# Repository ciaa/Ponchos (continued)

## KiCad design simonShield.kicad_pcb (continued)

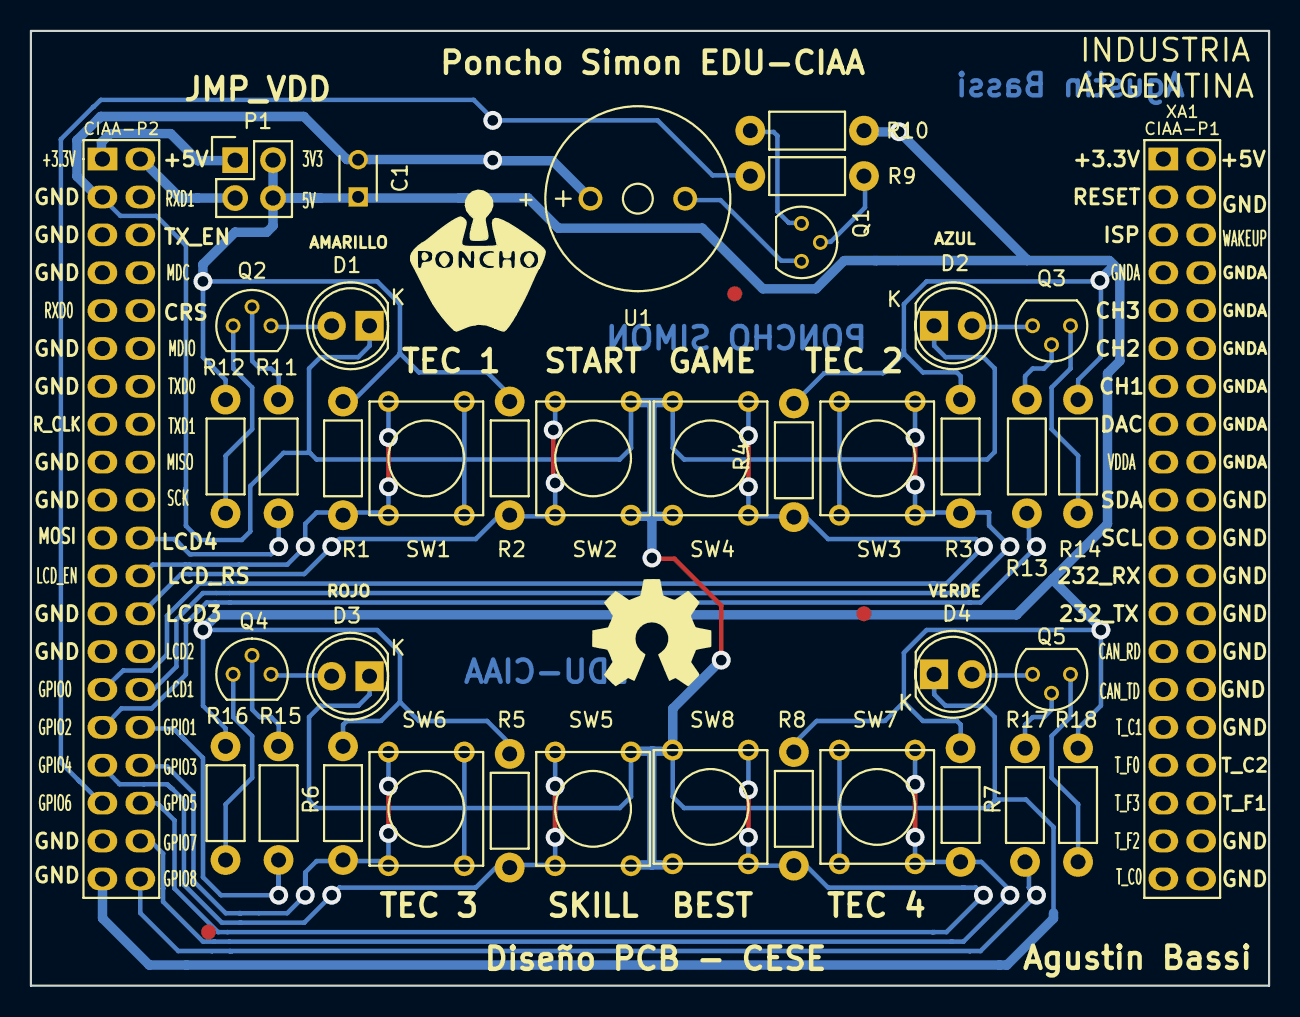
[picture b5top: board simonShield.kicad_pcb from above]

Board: 2 copper layers, 83.0 x 64.0 mm, 43 parts (0 on the bottom side), 32 nets.

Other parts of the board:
G101: Logo_OSHWA

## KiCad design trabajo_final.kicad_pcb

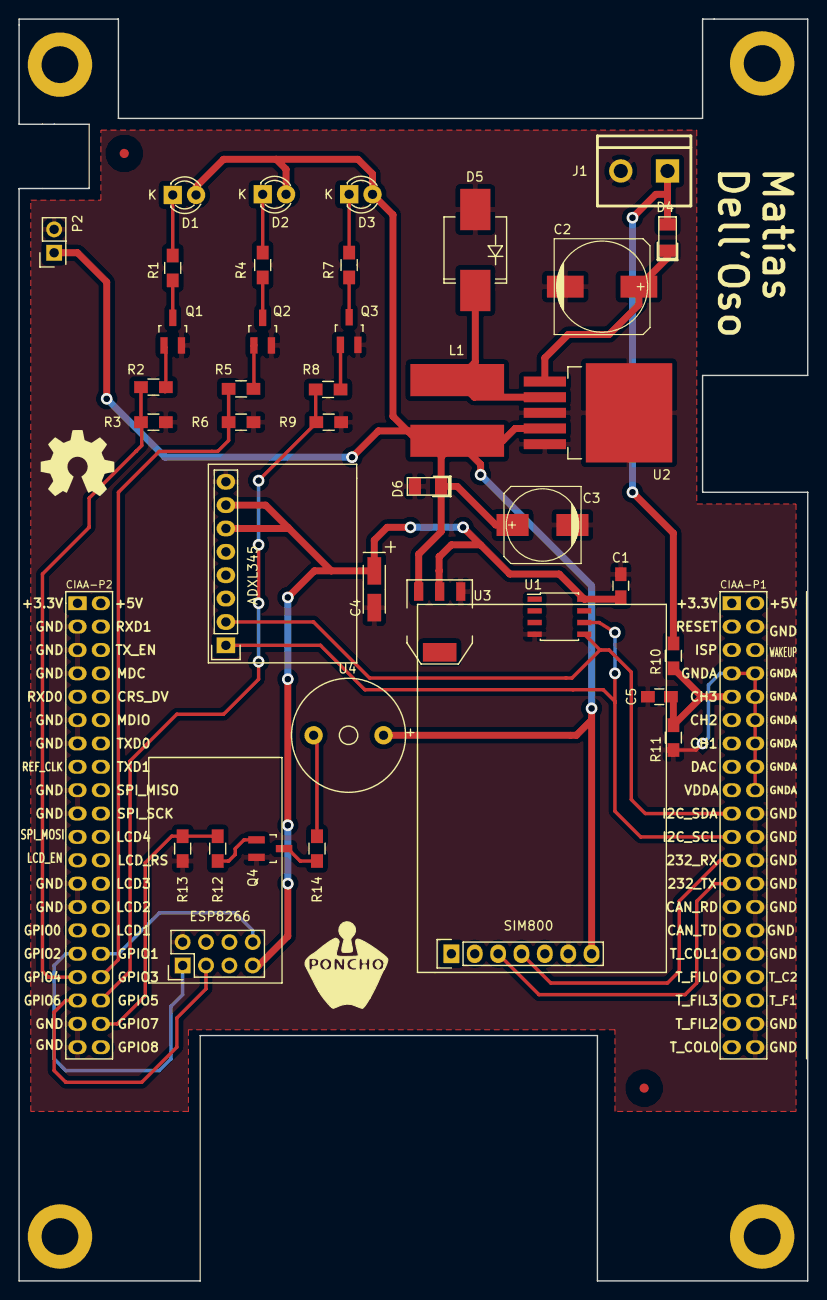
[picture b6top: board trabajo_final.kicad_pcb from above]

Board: 2 copper layers, 85.7 x 137.2 mm, 43 parts (0 on the bottom side), 30 nets.

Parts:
ADXL345: CONN_01X08; adxl345
C1, C5: 100nF; C_0805_HandSoldering
C2: 470uF; c2
C3: 330uF; c3
C4: 10uF; TantalC_SizeA_EIA-3216_HandSoldering
D1, D2, D3: LED; LED-3MM
D4: PMEG3020EH; SOD123F
D5: B540C-13-F; SMC_Handsoldering
D6: SMAZ5V6; SOD123F
ESP8266: CONN_02X04; esp8266
F1, F2: FIDUCIAL; Fiducial_1mm
G101: Logo_OSHWA
J1: TB_1X2; bornier2
L1: 47uH; SRN1060
P2: CONN_02X01; Pin_Header_Straight_2x01
Q1, Q2, Q3, Q4: 2N7002; SOT-23_Handsoldering
R1, R4, R7, R14: 680; R_0805_HandSoldering
R2, R5, R8, R12: 10K; R_0805_HandSoldering
R3, R6, R9, R13: 330K; R_0805_HandSoldering
R10: 470K; R_0805_HandSoldering
R11: 270K; R_0805_HandSoldering
SIM800: CONN_01X07; sim800l
U1: 24LC64; SOIC-8_3.9x4.9mm_Pitch1.27mm
U2: LM2596; TO-263-5Lead
U3: NCP1117ST33T3G; SOT-223
U4: Buzzer; Buzzer_12x9.5RM7.6
XA1: Conn_Poncho2P_2x_20x2; Conn_Poncho_Completo

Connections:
/Circuito Principal/ADC3: C5.2, R10.2, R11.1, XA1.9
/Circuito Principal/GPIO3: R5.2, R6.2, XA1.74
/Circuito Principal/GPIO4: R2.2, R3.2, XA1.73
/Circuito Principal/GPIO5: R8.2, R9.2, XA1.76
/Circuito Principal/GPIO6: ESP8266.3, XA1.75
/Circuito Principal/GPIO7: R12.1, R13.1, XA1.78
/Circuito Principal/RS232_RXD: SIM800.4, XA1.23
/Circuito Principal/RS232_TXD: SIM800.3, XA1.25
/Circuito Principal/SCL: ADXL345.1, U1.6, XA1.21
/Circuito Principal/SDA: ADXL345.2, U1.5, XA1.19
/Conector del Poncho/GPIO1: ESP8266.8, XA1.72
/Conector del Poncho/GPIO2: ESP8266.1, XA1.71
GND: ADXL345.8, C1.1, C2.2, C3.2, C4.2, C5.1, D5.1, D6.1, ESP8266.2, J1.2, P2.2, Q1.2, Q2.2, Q3.2, Q4.2, R3.1, R6.1, R9.1, R11.2, R13.2, SIM800.6, U1.4, U2.3, U2.5, U3.1, XA1.4, XA1.7, XA1.8, XA1.10, XA1.12, XA1.14, XA1.16, XA1.18, XA1.20, XA1.22, XA1.24, XA1.26, XA1.28, XA1.30, XA1.32, XA1.38, XA1.40, XA1.43, XA1.45, XA1.47, XA1.51, XA1.53, XA1.57, XA1.59, XA1.65, XA1.67, XA1.77, XA1.79
unnamed: C2.1, D4.2, U2.1
unnamed: D1.1, R1.2
unnamed: D2.1, R4.2
unnamed: D3.1, R7.2
unnamed: D4.1, J1.1, R10.1
unnamed: D5.2, L1.1, U2.2
unnamed: Q1.1, R2.1
unnamed: Q1.3, R1.1
unnamed: Q2.1, R5.1
unnamed: Q2.3, R4.1
unnamed: Q3.1, R8.1
unnamed: Q3.3, R7.1
unnamed: Q4.1, R12.2
unnamed: Q4.3, R14.2
unnamed: R14.1, U4.2
VCC: C3.1, D1.2, D2.2, D3.2, D6.2, L1.2, P2.1, SIM800.7, U2.4, U3.3, U4.1
VDD: ADXL345.6, ADXL345.7, C1.2, C4.1, ESP8266.7, U1.8, U3.2
